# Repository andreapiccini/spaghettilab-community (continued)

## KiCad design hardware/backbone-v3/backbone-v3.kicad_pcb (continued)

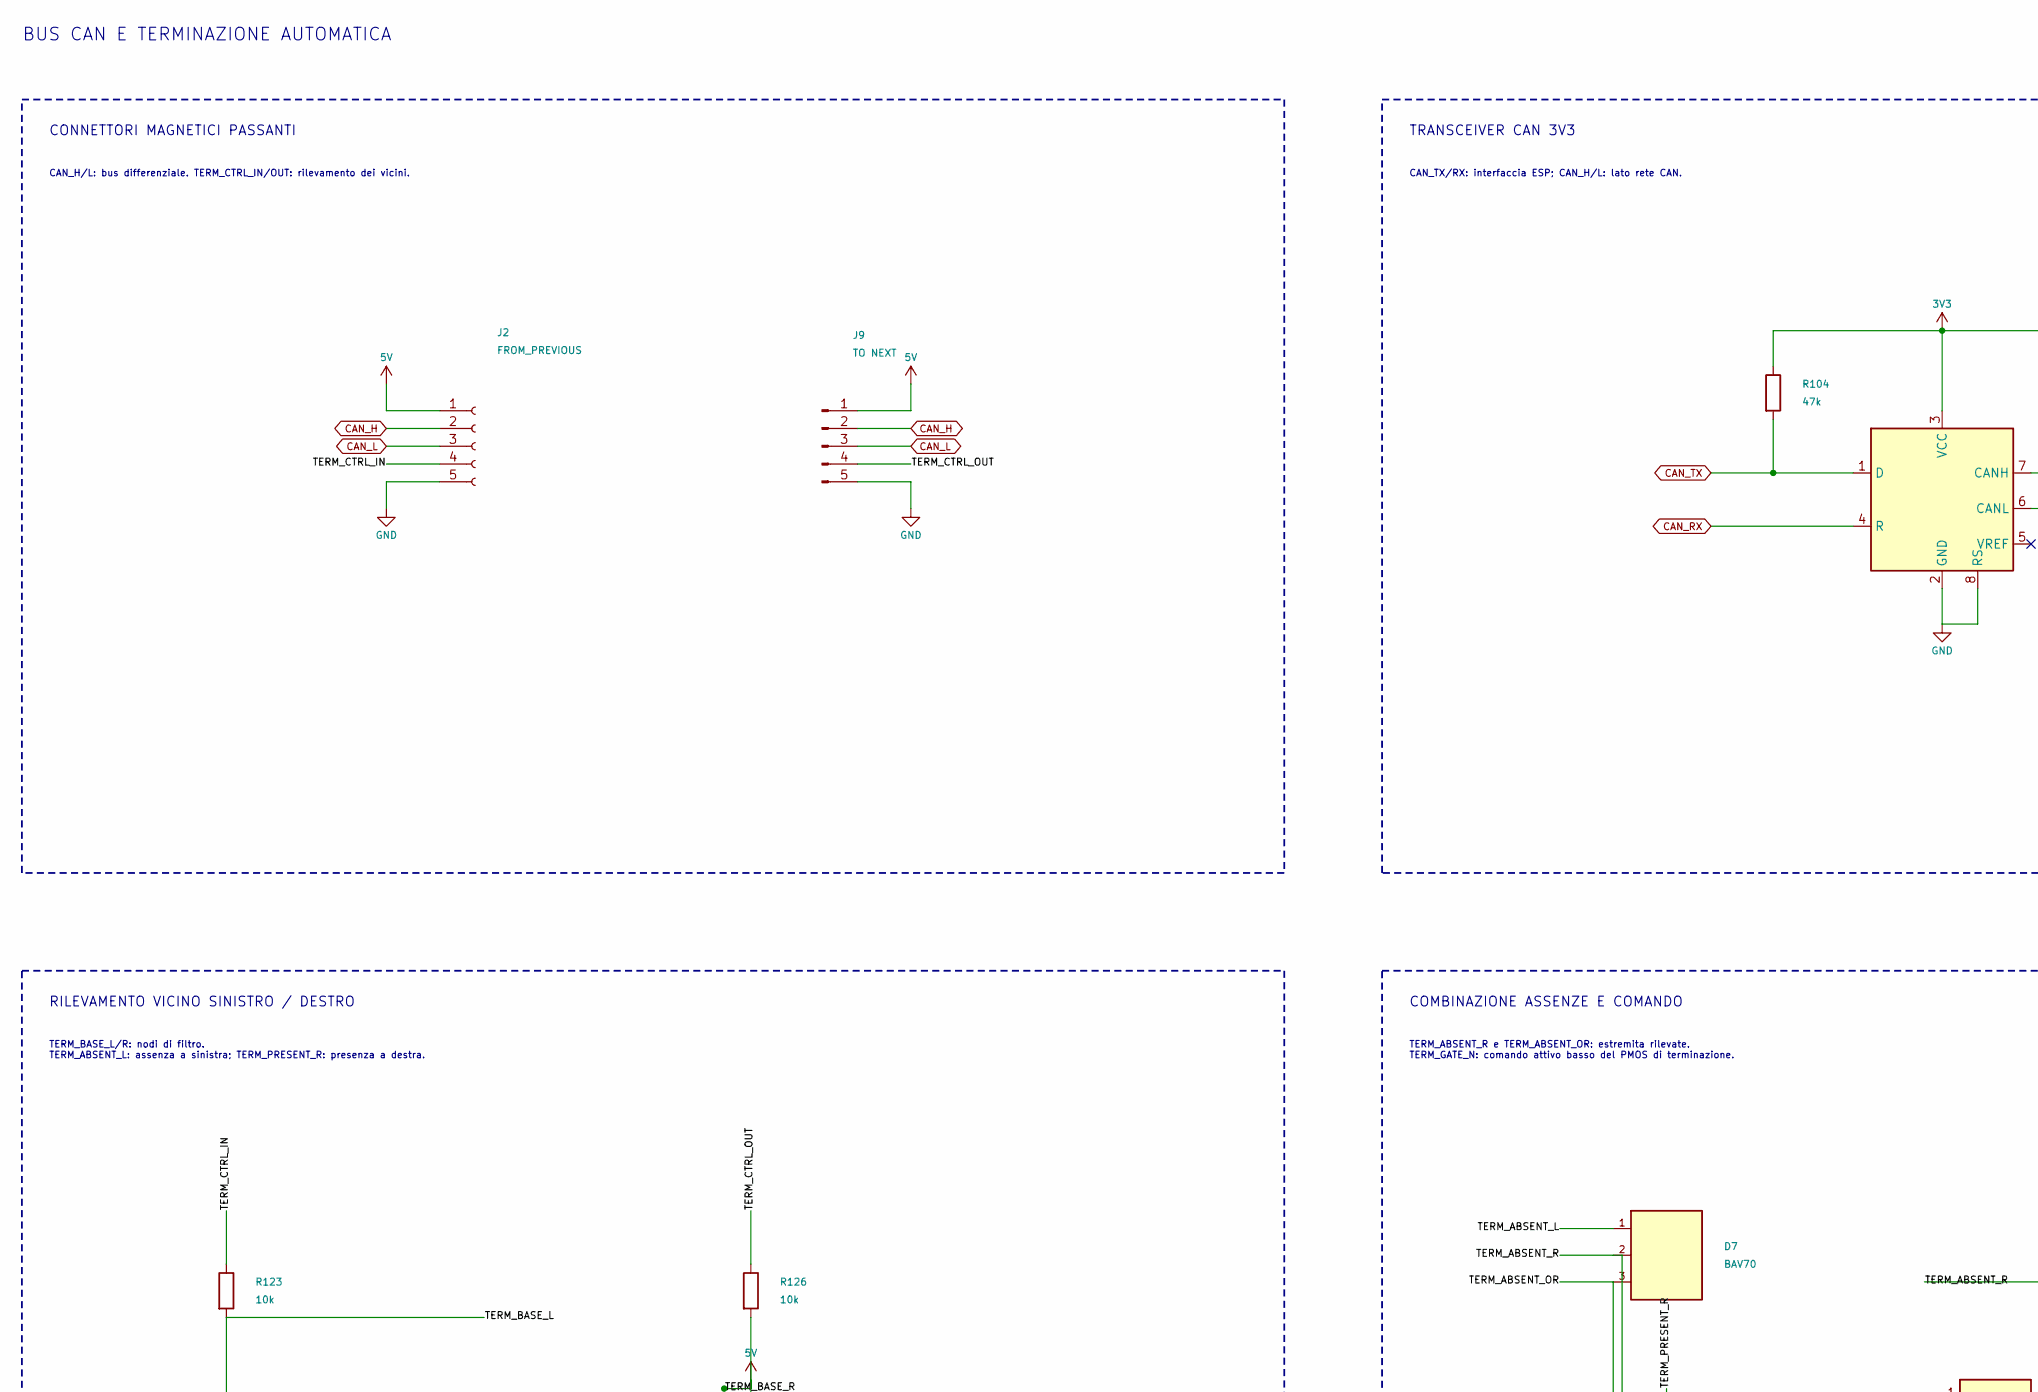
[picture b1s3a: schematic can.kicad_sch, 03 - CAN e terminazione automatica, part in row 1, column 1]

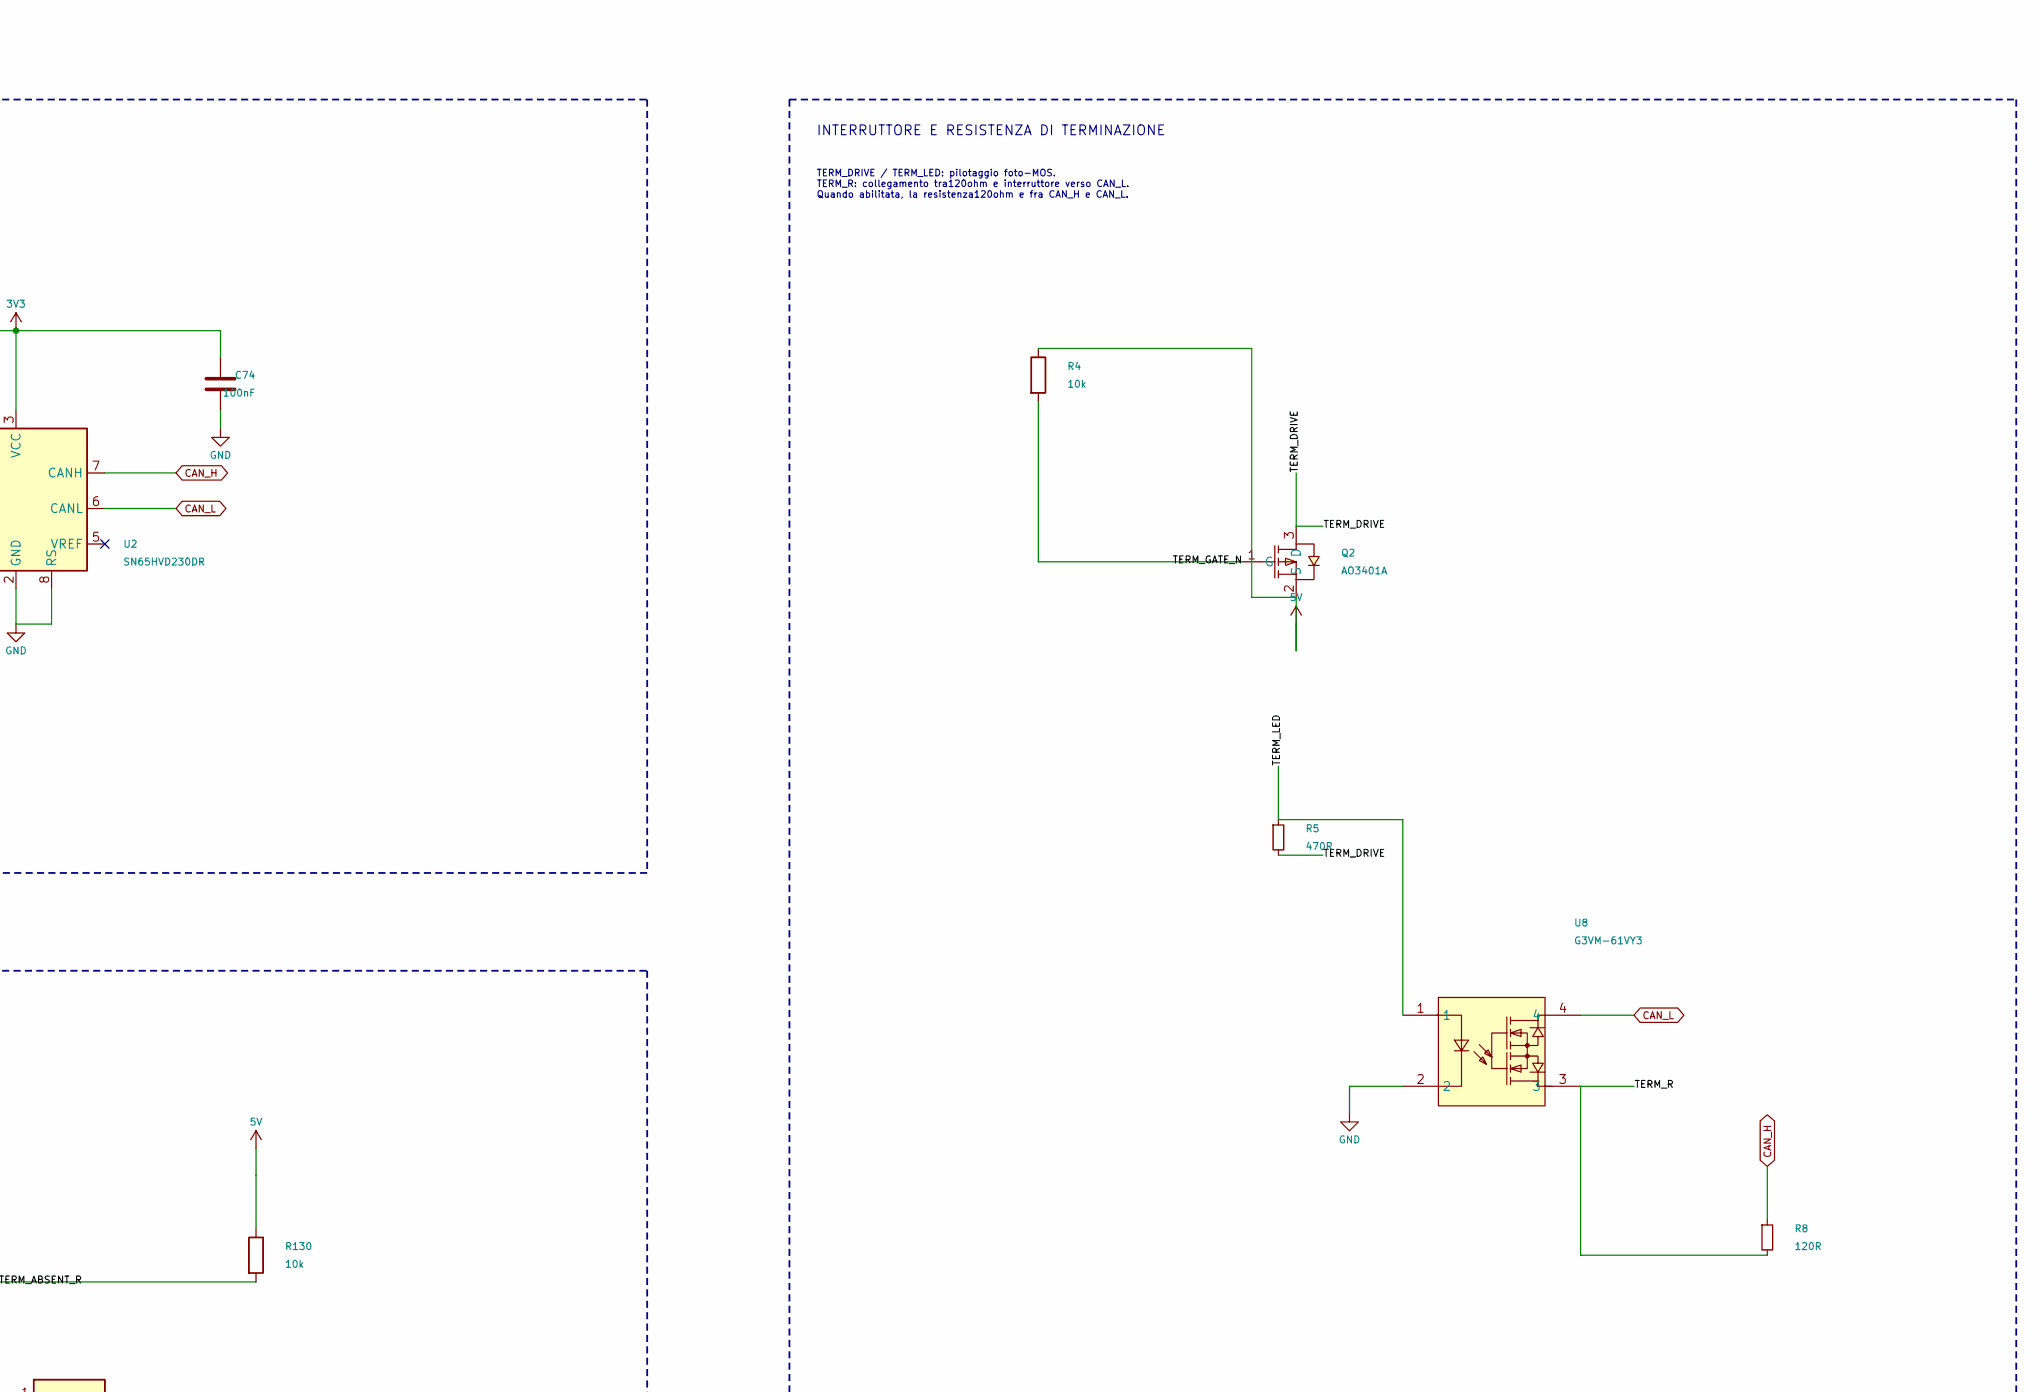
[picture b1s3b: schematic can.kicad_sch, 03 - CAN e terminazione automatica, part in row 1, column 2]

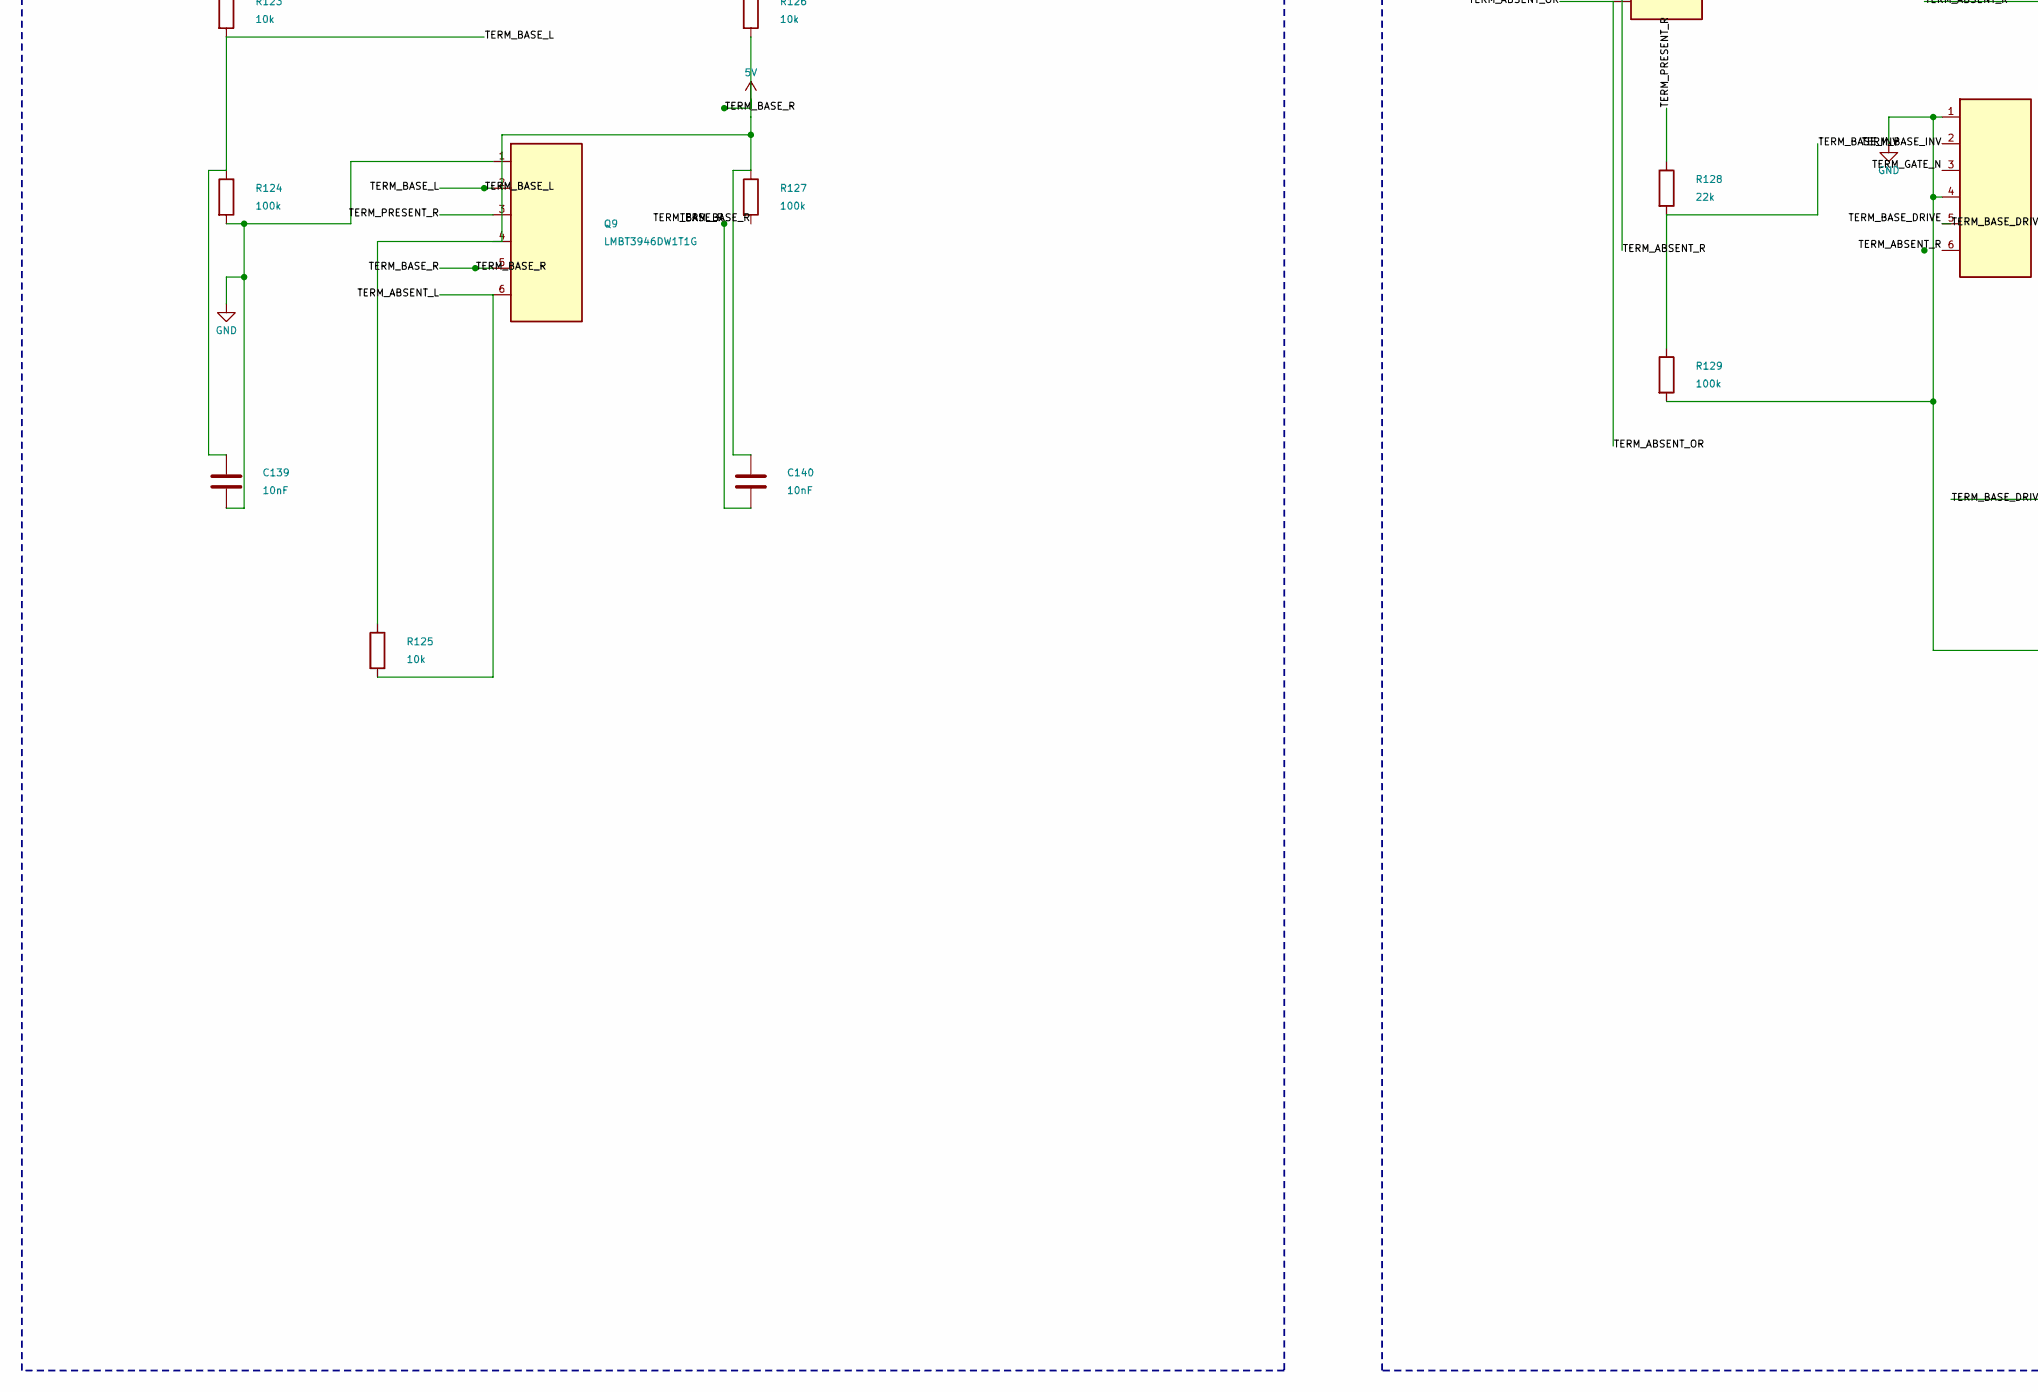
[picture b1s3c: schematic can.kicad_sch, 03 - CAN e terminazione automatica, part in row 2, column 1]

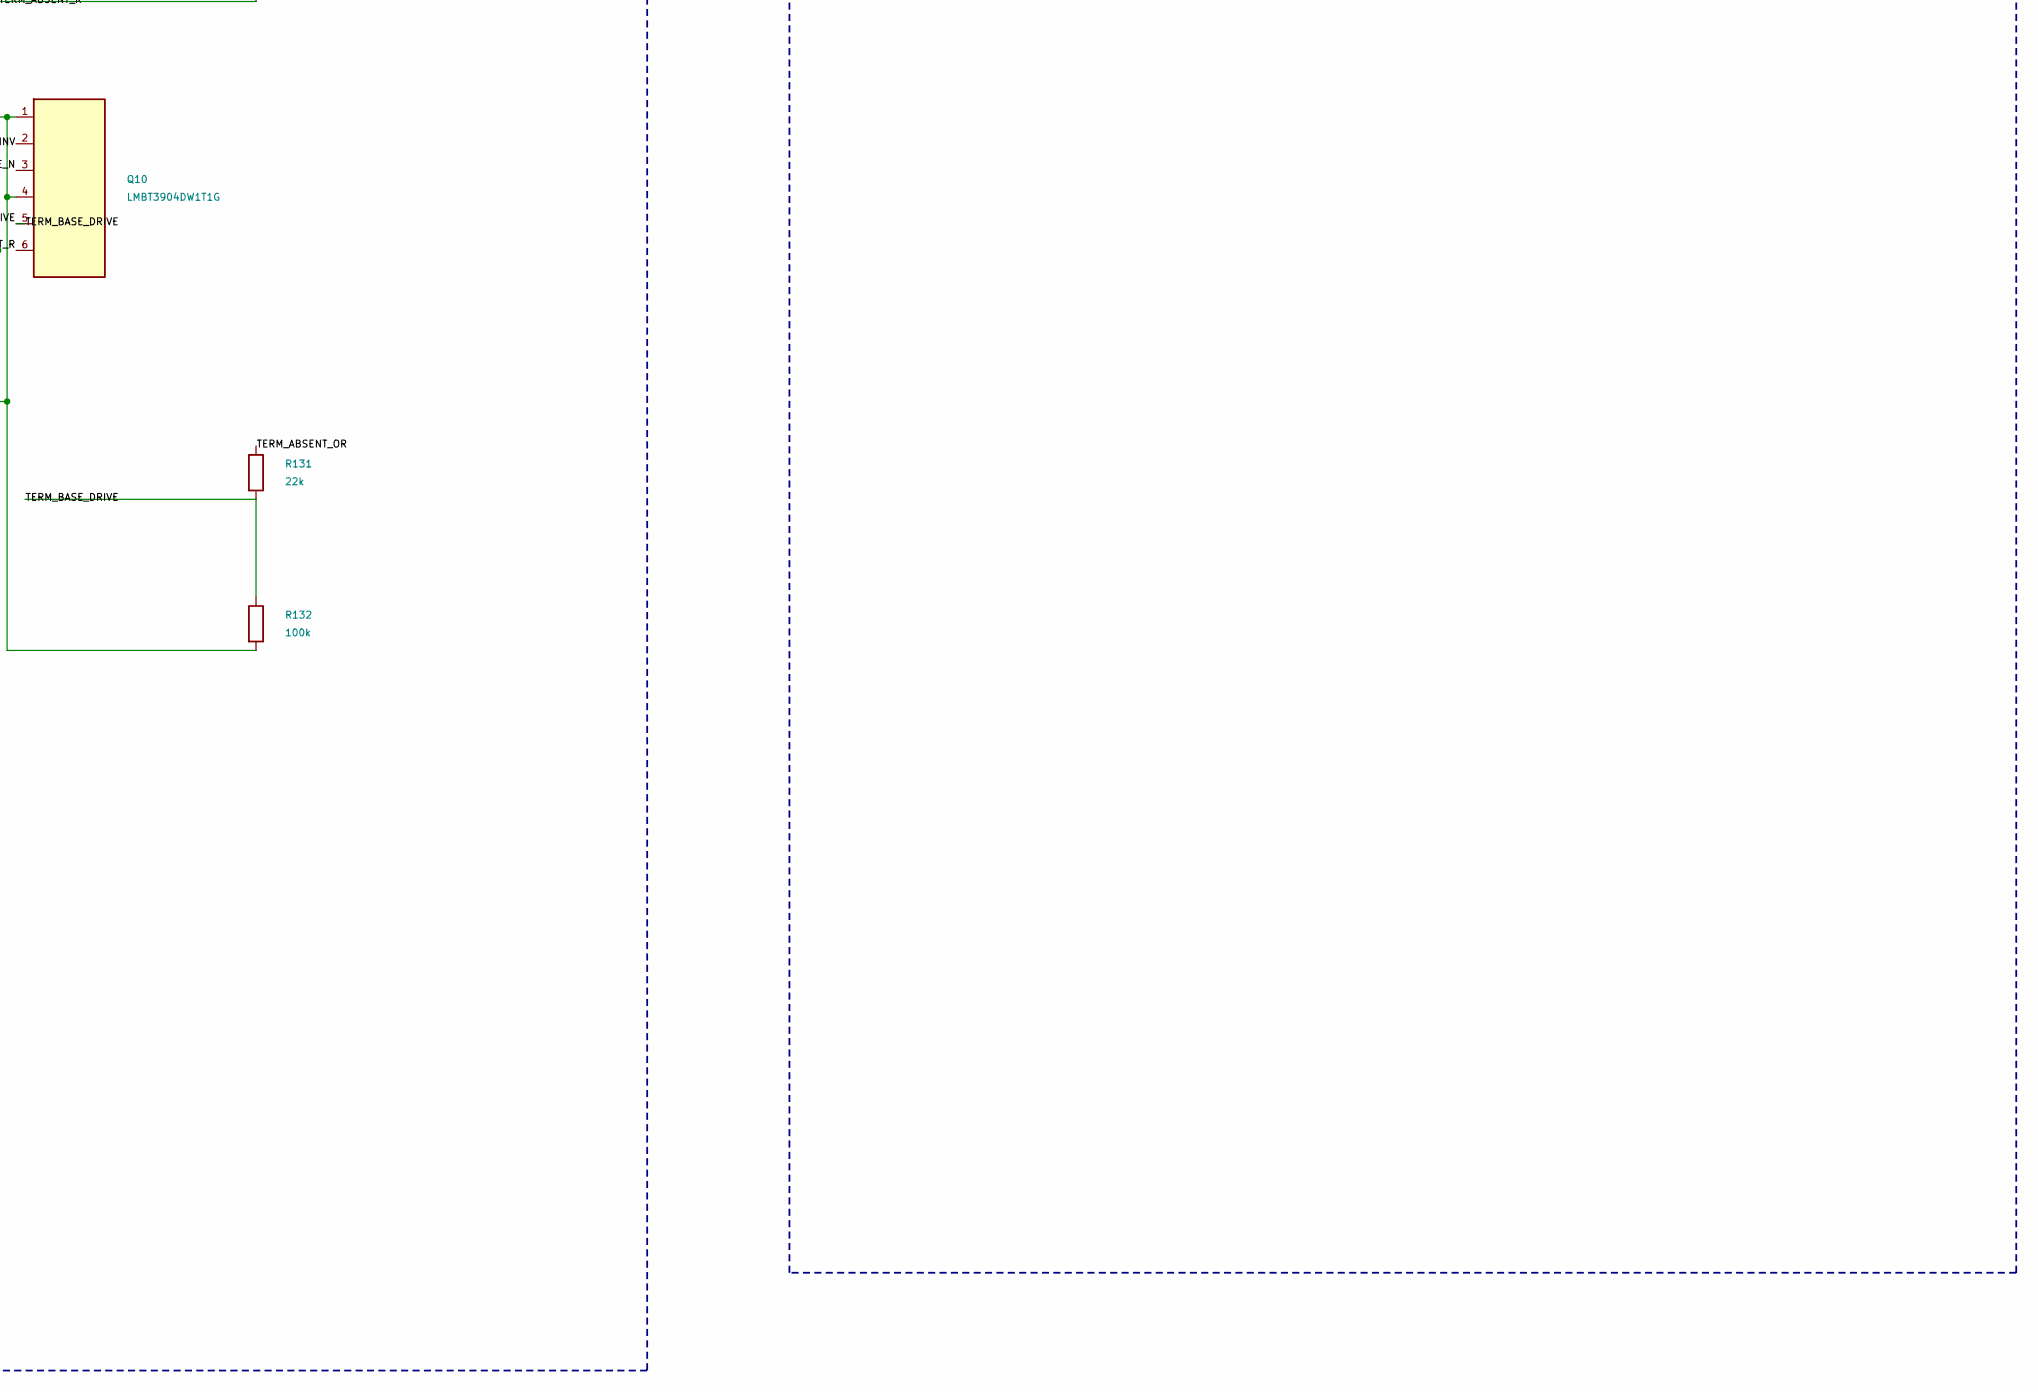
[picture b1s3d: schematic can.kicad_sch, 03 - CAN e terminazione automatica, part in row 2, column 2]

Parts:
C74: 100nF; C_0603_1608Metric
C139, C140: 10nF; C_0603_1608Metric; MPN CL10B103KB8NNNC; LCSC C1589
D7: BAV70; SOT-23; MPN BAV70; LCSC C68978
J2: FROM_PREVIOUS; Magnetic_J2_PTH_Module
J9: TO NEXT; Magnetic_J9_PTH_Module
Q2: AO3401A; SOT-23_L2.9-W1.3-P1.90-LS2.4-BR; MPN AO3401A; LCSC Part C15127
Q9: LMBT3946DW1T1G; SOT-363_SC-70-6; MPN LMBT3946DW1T1G; LCSC C136169
Q10: LMBT3904DW1T1G; SOT-363_SC-70-6; MPN LMBT3904DW1T1G; LCSC C131781
R4: 10k; R_0603_1608Metric
R5: 470R; R0603; MPN 0603WAF4700T5E; LCSC Part Name C23179
R8: 120R; R0603; MPN 0603WAF1200T5E; LCSC Part Name C2906988
R104: 47k; R_0603_1608Metric; MPN 0603WAF4702T5E; LCSC C25819
R123, R125, R126, R130: 10k; R_0603_1608Metric; MPN 0603WAF1002T5E; LCSC C25804
R124, R127, R129, R132: 100k; R_0603_1608Metric; MPN 0603WAF1003T5E; LCSC C25803
R128, R131: 22k; R_0603_1608Metric; MPN 0603WAF2202T5E; LCSC C31850
U2: SN65HVD230DR; SOIC-8_L4.9-W3.9-P1.27-LS6.0-BL; MPN SN65HVD230DR; LCSC Part C12084
U8: G3VM-61VY3; SMD-4_L4.6-W3.7-P2.54-LS7.0-TL; MPN G3VM-61VY3(TR); LCSC Part C2152318

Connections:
3V3: C74.2, R104.1, U2.3 (VCC); also elsewhere on the board
/03 - CAN e terminazione automatica/TERM_ABSENT_L: D7.1 (A), Q9.6 (C), R125.2
/03 - CAN e terminazione automatica/TERM_ABSENT_OR: D7.3 (K), R131.1
/03 - CAN e terminazione automatica/TERM_ABSENT_R: D7.2 (A), Q10.6 (C), R130.2
/03 - CAN e terminazione automatica/TERM_BASE_DRIVE: Q10.5 (B), R131.2, R132.1
/03 - CAN e terminazione automatica/TERM_BASE_INV: Q10.2 (B), R128.2, R129.1
/03 - CAN e terminazione automatica/TERM_BASE_L: C139.1, Q9.2 (B), R123.2, R124.1
/03 - CAN e terminazione automatica/TERM_CTRL_IN: J2.4, R123.1
/03 - CAN e terminazione automatica/TERM_CTRL_OUT: J9.4, R126.1
/03 - CAN e terminazione automatica/TERM_DRIVE: Q2.3 (D), R5.2
/03 - CAN e terminazione automatica/TERM_GATE_N: Q2.1 (G), Q10.3 (C), R4.2
/03 - CAN e terminazione automatica/TERM_LED: R5.1, U8.1
/03 - CAN e terminazione automatica/TERM_PRESENT_R: Q9.3 (C), R128.1
/03 - CAN e terminazione automatica/TERM_R: R8.2, U8.3
CAN_H: J2.2, J9.2, R8.1, U2.7 (CANH)
CAN_L: J2.3, J9.3, U2.6 (CANL), U8.4
CAN_RX: U2.4 (R); also elsewhere on the board
CAN_TX: R104.2, U2.1 (D); also elsewhere on the board
GND: C74.1, C139.2, J2.5, J9.5, Q9.1 (E), Q10.1 (E), Q10.4 (E), R124.2, R129.2, R132.2, U2.2 (GND), U2.8 (RS), U8.2; also elsewhere on the board

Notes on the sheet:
COMBINAZIONE ASSENZE E COMANDO
RILEVAMENTO VICINO SINISTRO / DESTRO
CAN_H/L: bus differenziale. TERM_CTRL_IN/OUT: rilevamento dei vicini.
TERM_BASE_L/R: nodi di filtro. TERM_ABSENT_L: assenza a sinistra; TERM_PRESENT_R: presenza a destra.
INTERRUTTORE E RESISTENZA DI TERMINAZIONE
CONNETTORI MAGNETICI PASSANTI
BUS CAN E TERMINAZIONE AUTOMATICA
TRANSCEIVER CAN 3V3
TERM_ABSENT_R e TERM_ABSENT_OR: estremita rilevate. TERM_GATE_N: comando attivo basso del PMOS di terminazione.
TERM_DRIVE / TERM_LED: pilotaggio foto-MOS. TERM_R: collegamento tra120ohm e interruttore verso CAN_L. Quando abilitata, la resistenza120ohm e fra CAN_H e CAN_L.
CAN_TX/RX: interfaccia ESP; CAN_H/L: lato rete CAN.

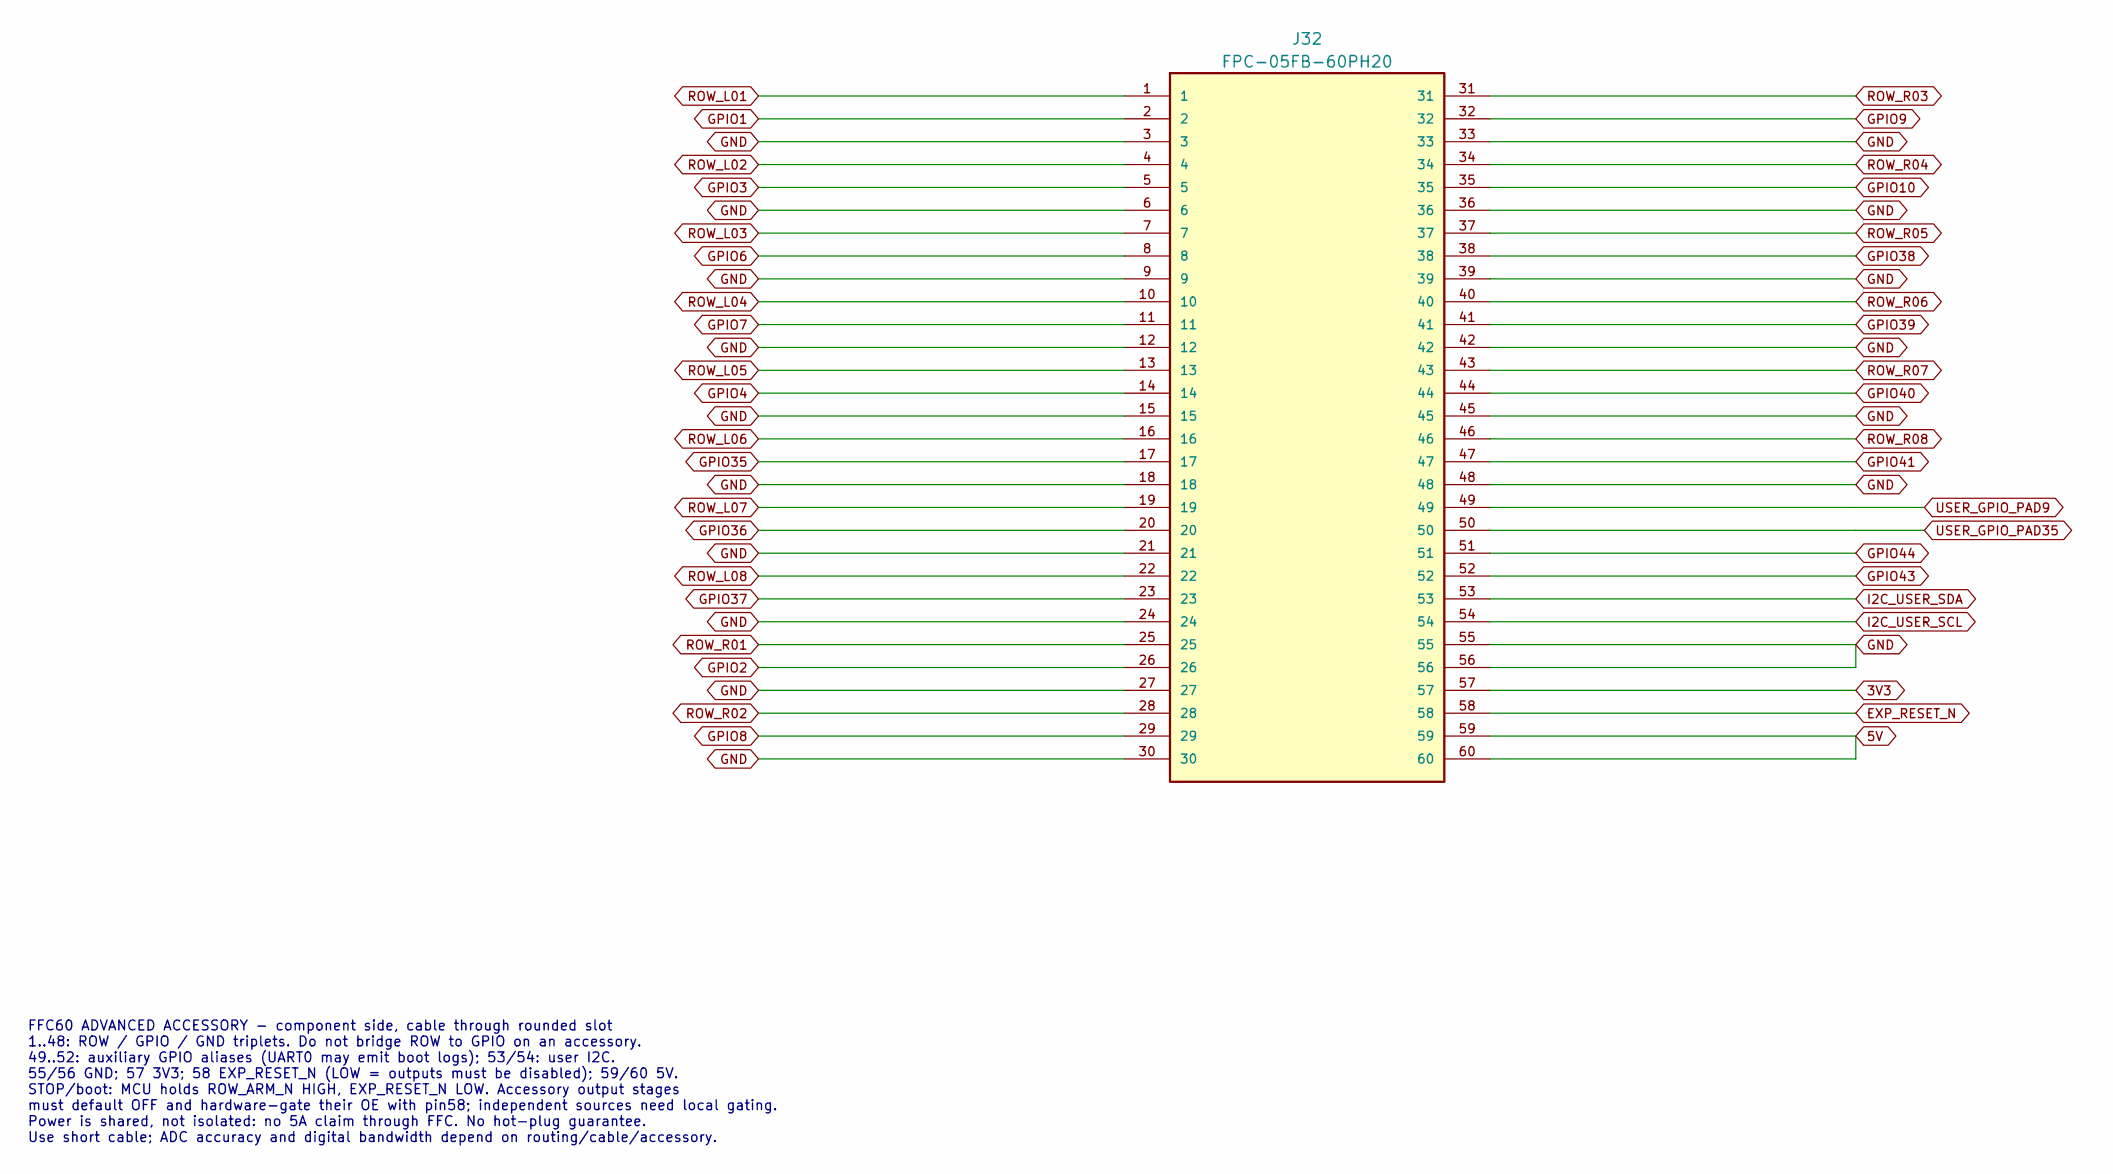
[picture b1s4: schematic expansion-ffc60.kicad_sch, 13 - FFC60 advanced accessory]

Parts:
J32: FPC-05FB-60PH20; XUNPU_FPC-05FB-60PH20; LCSC Part C2856839

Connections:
3V3: J32.57; also elsewhere on the board
EXP_RESET_N: J32.58; also elsewhere on the board
GND: J32.3, J32.6, J32.9, J32.12, J32.15, J32.18, J32.21, J32.24, J32.27, J32.30, J32.33, J32.36, J32.39, J32.42, J32.45, J32.48, J32.55, J32.56; also elsewhere on the board
GPIO1: J32.2; also elsewhere on the board
GPIO2: J32.26; also elsewhere on the board
GPIO3: J32.5; also elsewhere on the board
GPIO4: J32.14; also elsewhere on the board
GPIO6: J32.8; also elsewhere on the board
GPIO7: J32.11; also elsewhere on the board
GPIO8: J32.29; also elsewhere on the board
GPIO9: J32.32; also elsewhere on the board
GPIO10: J32.35; also elsewhere on the board
GPIO35: J32.17; also elsewhere on the board
GPIO36: J32.20; also elsewhere on the board
GPIO37: J32.23; also elsewhere on the board
GPIO38: J32.38; also elsewhere on the board
GPIO39: J32.41; also elsewhere on the board
GPIO40: J32.44; also elsewhere on the board
GPIO41: J32.47; also elsewhere on the board
GPIO43: J32.52; also elsewhere on the board
GPIO44: J32.51; also elsewhere on the board
I2C_USER_SCL: J32.54; also elsewhere on the board
I2C_USER_SDA: J32.53; also elsewhere on the board
ROW_L01: J32.1; also elsewhere on the board
ROW_L02: J32.4; also elsewhere on the board
ROW_L03: J32.7; also elsewhere on the board
ROW_L04: J32.10; also elsewhere on the board
ROW_L05: J32.13; also elsewhere on the board
ROW_L06: J32.16; also elsewhere on the board
ROW_L07: J32.19; also elsewhere on the board
ROW_L08: J32.22; also elsewhere on the board
ROW_R01: J32.25; also elsewhere on the board
ROW_R02: J32.28; also elsewhere on the board
ROW_R03: J32.31; also elsewhere on the board
ROW_R04: J32.34; also elsewhere on the board
ROW_R05: J32.37; also elsewhere on the board
ROW_R06: J32.40; also elsewhere on the board
ROW_R07: J32.43; also elsewhere on the board
ROW_R08: J32.46; also elsewhere on the board
USER_GPIO_PAD9: J32.49; also elsewhere on the board
USER_GPIO_PAD35: J32.50; also elsewhere on the board

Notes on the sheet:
FFC60 ADVANCED ACCESSORY - component side, cable through rounded slot 1..48: ROW / GPIO / GND triplets. Do not bridge ROW to GPIO on an accessory. 49..52: auxiliary GPIO aliases (UART0 may emit boot logs); 53/54: user I2C. 55/56 GND; 57 3V3; 58 EXP_RESET_N (LOW = outputs must be disabled); 59/60 5V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

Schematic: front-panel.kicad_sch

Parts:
C400, C402, C944: 100nF; C_0402_1005Metric
C401: 1uF; C_0402_1005Metric
D700, D704, D708, D712, D716, D720, D724, D728, D732, D736, D740, D744, D748, D752, D756, D760, D775: XL-1005UOC; LED_0402_1005Metric; LCSC Part C965791
D701, D705, D709, D713, D717, D721, D725, D729, D733, D737, D741, D745, D749, D753, D757, D761, D785, D787, D788, D789, D790, D791, D792, D793, D794, D797, D798, D800, D801, D802, D803, D804: XL-1005UBC; LED_0402_1005Metric; LCSC Part C965795
D702, D706, D710, D714, D718, D722, D726, D730, D734, D738, D742, D746, D750, D754, D758, D762, D764, D765, D766: XL-1005UGC; LED_0402_1005Metric; LCSC Part C965793
D703, D707, D711, D715, D719, D723, D727, D731, D735, D739, D743, D747, D751, D755, D759, D763, D776, D782: XL-1005UWC; LED_0402_1005Metric; LCSC Part C20613596
D767, D768, D769, D770, D772, D779, D780, D781, D783, D784: XL-1608UWWC-A; LED_0603_1608Metric; LCSC Part C55338549
D771, D777, D778: XL-1608UOC-06; LED_0603_1608Metric; LCSC Part C965800
D773: XL-1608UGGC; LED_0603_1608Metric; LCSC Part C55338548
D774, D786, D795, D796, D799: XL-1608UBC-04; LED_0603_1608Metric; LCSC Part C965807
H1, H2, H3, H4: MountingHole; MountingHole_2.2mm_M2_DIN965
R400: 47k; R_0402_1005Metric
R972: 100k; R_0402_1005Metric
TE1: TOUCH_NEXT; Annular_Touch_Large
TE2: TOUCH_MODE; Annular_Touch_Large
TE3: TOUCH_PLAY_STOP; Annular_Touch_Small
TE4: TOUCH_LOAD_SAVE; Annular_Touch_Small
U70: IS31FL3731-QFLS2-TR; IS31FL3731_QFN28_4x4; LCSC Part C191206
U94: BS8112A-3; SOIC-16_3.9x9.9mm_P1.27mm; LCSC Part C91296

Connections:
3V3: C944.1, U94.12 (VDD); also elsewhere on the board
ESP_EN: U70.3 (SDB); also elsewhere on the board
ESP_GPIO45_STRAP: R972.1; also elsewhere on the board
GND: C400.2, C401.2, C402.2, C944.2, R400.2, R972.2, U70.5 (GND), U70.17 (IN), U70.18 (AD), U70.29 (EP), U94.11 (VSS); also elsewhere on the board
I2C_INT_SCL: U70.20 (SCL), U94.13 (SCL); also elsewhere on the board
I2C_INT_SDA: U70.19 (SDA), U94.14 (SDA); also elsewhere on the board
LABEL_CA1: D700.1 (K), D701.1 (K), D702.1 (K), D703.1 (K), D704.1 (K), D705.1 (K), D706.1 (K), D707.1 (K), D708.2 (A), D716.2 (A), D724.2 (A), D732.2 (A), D740.2 (A), D748.2 (A), D756.2 (A), D764.2 (A), U70.21 (CA1)
LABEL_CA2: D700.2 (A), D708.1 (K), D709.1 (K), D710.1 (K), D711.1 (K), D712.1 (K), D713.1 (K), D714.1 (K), D715.1 (K), D717.2 (A), D725.2 (A), D733.2 (A), D741.2 (A), D749.2 (A), D757.2 (A), D765.2 (A), U70.22 (CA2)
LABEL_CA3: D701.2 (A), D709.2 (A), D716.1 (K), D717.1 (K), D718.1 (K), D719.1 (K), D720.1 (K), D721.1 (K), D722.1 (K), D723.1 (K), D726.2 (A), D734.2 (A), D742.2 (A), D750.2 (A), D758.2 (A), D766.2 (A), U70.23 (CA3)
LABEL_CA4: D702.2 (A), D710.2 (A), D718.2 (A), D724.1 (K), D725.1 (K), D726.1 (K), D727.1 (K), D728.1 (K), D729.1 (K), D730.1 (K), D731.1 (K), D735.2 (A), D743.2 (A), D751.2 (A), D759.2 (A), D767.2 (A), U70.24 (CA4)
LABEL_CA5: D703.2 (A), D711.2 (A), D719.2 (A), D727.2 (A), D732.1 (K), D733.1 (K), D734.1 (K), D735.1 (K), D736.1 (K), D737.1 (K), D738.1 (K), D739.1 (K), D744.2 (A), D752.2 (A), D760.2 (A), D768.2 (A), U70.25 (CA5)
LABEL_CA6: D704.2 (A), D712.2 (A), D720.2 (A), D728.2 (A), D736.2 (A), D740.1 (K), D741.1 (K), D742.1 (K), D743.1 (K), D744.1 (K), D745.1 (K), D746.1 (K), D747.1 (K), D753.2 (A), D761.2 (A), D769.2 (A), U70.26 (CA6)
LABEL_CA7: D705.2 (A), D713.2 (A), D721.2 (A), D729.2 (A), D737.2 (A), D745.2 (A), D748.1 (K), D749.1 (K), D750.1 (K), D751.1 (K), D752.1 (K), D753.1 (K), D754.1 (K), D755.1 (K), D762.2 (A), D770.2 (A), U70.27 (CA7)
LABEL_CA8: D706.2 (A), D714.2 (A), D722.2 (A), D730.2 (A), D738.2 (A), D746.2 (A), D754.2 (A), D756.1 (K), D757.1 (K), D758.1 (K), D759.1 (K), D760.1 (K), D761.1 (K), D762.1 (K), D763.1 (K), D771.2 (A), U70.28 (CA8)
LABEL_CA9: D707.2 (A), D715.2 (A), D723.2 (A), D731.2 (A), D739.2 (A), D747.2 (A), D755.2 (A), D763.2 (A), D764.1 (K), D765.1 (K), D766.1 (K), D767.1 (K), D768.1 (K), D769.1 (K), D770.1 (K), D771.1 (K), U70.1 (CA9)
LABEL_CB1: D772.1 (K), D773.1 (K), D774.1 (K), D775.1 (K), D776.1 (K), D777.1 (K), D778.1 (K), D779.1 (K), D780.2 (A), D788.2 (A), D796.2 (A), D804.2 (A), U70.7 (CB1)
LABEL_CB2: D772.2 (A), D780.1 (K), D781.1 (K), D782.1 (K), D783.1 (K), D784.1 (K), D785.1 (K), D786.1 (K), D787.1 (K), D789.2 (A), D797.2 (A), U70.8 (CB2)
LABEL_CB3: D773.2 (A), D781.2 (A), D788.1 (K), D789.1 (K), D790.1 (K), D791.1 (K), D792.1 (K), D793.1 (K), D794.1 (K), D795.1 (K), D798.2 (A), U70.9 (CB3)
LABEL_CB4: D774.2 (A), D782.2 (A), D790.2 (A), D796.1 (K), D797.1 (K), D798.1 (K), D799.1 (K), D800.1 (K), D801.1 (K), D802.1 (K), D803.1 (K), U70.10 (CB4)
LABEL_CB5: D775.2 (A), D783.2 (A), D791.2 (A), D799.2 (A), D804.1 (K), U70.11 (CB5)
LABEL_CB6: D776.2 (A), D784.2 (A), D792.2 (A), D800.2 (A), U70.12 (CB6)
LABEL_CB7: D777.2 (A), D785.2 (A), D793.2 (A), D801.2 (A), U70.13 (CB7)
LABEL_CB8: D778.2 (A), D786.2 (A), D794.2 (A), D802.2 (A), U70.14 (CB8)
LABEL_CB9: D779.2 (A), D787.2 (A), D795.2 (A), D803.2 (A), U70.15 (CB9)
LABEL_C_FILT: C402.1, U70.16 (C_FILT)
LABEL_R_EXT: R400.1, U70.6 (R_EXT)
TOUCH_LOAD_SAVE: TE4.1, U94.2 (KEY4)
TOUCH_MODE: TE2.1, U94.1 (KEY3)
TOUCH_NEXT: TE1.1, U94.16 (KEY2)
TOUCH_PLAY_STOP: TE3.1, U94.15 (KEY1)

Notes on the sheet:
ROW 13 OFF
LOGO 14
Wi-Fi
ROW 02 OFF
ROW 14 MCU
ROW 16 GND
ROW 06 VCC
IS31FL3731 / two independent charlieplex matrices / 0x74
PLAY
STOP
ROW 02 GND
ROW 08 VCC
Four capacitive keys / BS8112A-3 / internal I2C at 0x50
ROW 11 VCC
SAVE
LOGO 15
ROW 04 MCU
CA and CB are separate. For each LED use two different lines of its own matrix.
MASTER
BACKBONE V3 / FOUR TOUCH KEYS AND FRONT-PANEL LEDS
ROW 03 GND
LOCK
BAT 3
ROW 03 MCU
LOGO 03
ROW 10 MCU
ROW 16 VCC
ROW 01 VCC
ROW 03 OFF
LOGO 12
LOGO 10
LOGO 02
ROW 04 OFF
CONTROL, MEMORY AND STATUS LEDS / LOGO BACKLIGHT
ROW 11 MCU
VCC 3.3V 2
Bluetooth
Unused inputs and KEY12/IRQ are left open.
LOGO 04
LOGO 19

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
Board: 4 copper layers, 257 parts (5 on the bottom side), 152 nets, no tracks yet.
